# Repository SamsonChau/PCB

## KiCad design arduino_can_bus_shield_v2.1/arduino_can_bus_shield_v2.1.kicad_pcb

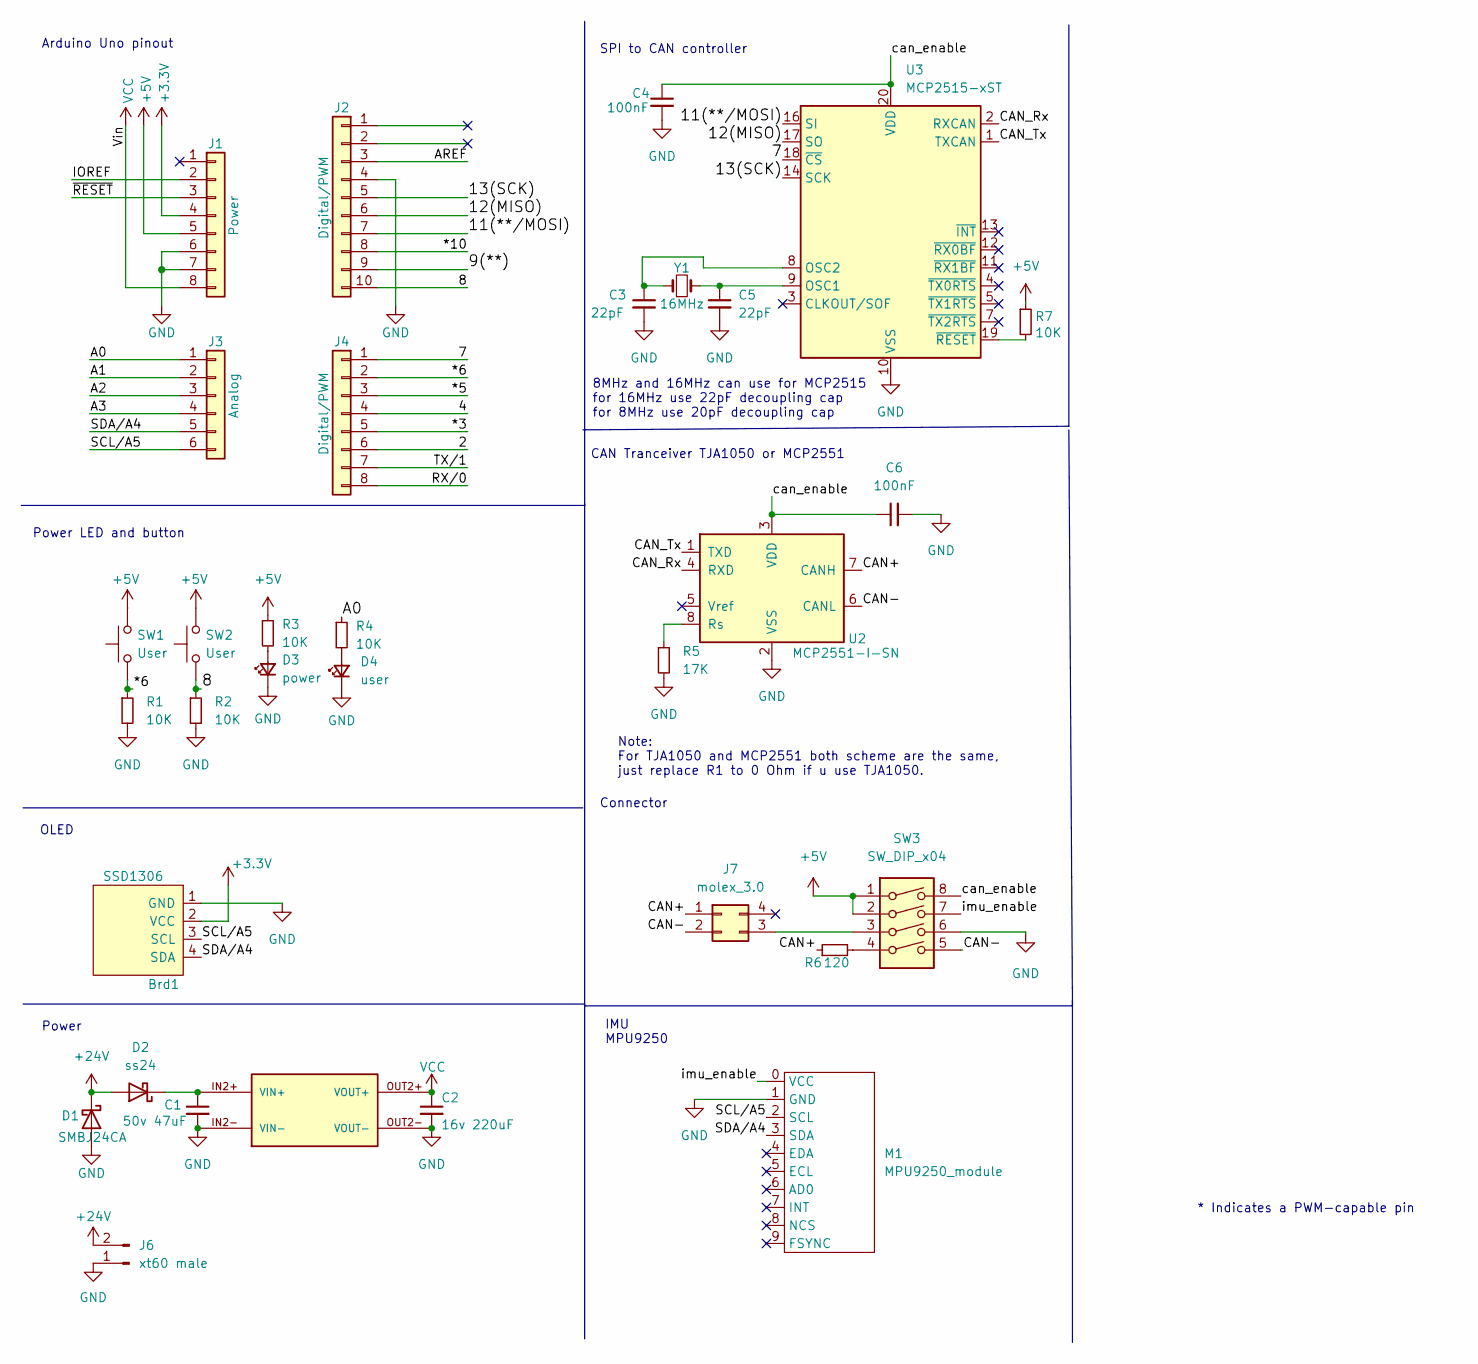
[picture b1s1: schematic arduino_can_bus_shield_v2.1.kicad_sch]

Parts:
Brd1: SSD1306; 128x64OLED
C1: 50v 47uF; C_Elec_6.3x7.7
C2: 16v 220uF; C_Elec_6.3x7.7
C3, C5: 22pF; C_0805_2012Metric_Pad1.18x1.45mm_HandSolder
C4, C6: 100nF; C_0805_2012Metric_Pad1.18x1.45mm_HandSolder
D1: SMBJ24CA; D_SMB_Handsoldering
D2: ss24; D_SMB_Handsoldering
D3: power; LED_0805_2012Metric_Pad1.15x1.40mm_HandSolder
D4: user; LED_0805_2012Metric_Pad1.15x1.40mm_HandSolder
J1: Power; PinSocket_1x08_P2.54mm_Vertical
J2: Digital/PWM; PinSocket_1x10_P2.54mm_Vertical
J3: Analog; PinSocket_1x06_P2.54mm_Vertical
J4: Digital/PWM; PinSocket_1x08_P2.54mm_Vertical
J6: xt60 male; XT60PW-M20
J7: molex_3.0; Molex_Micro-Fit_3.0_43045-0400_2x02_P3.00mm_Horizontal
M1: MPU9250_module
R1, R2, R3, R4, R7: 10K; R_0805_2012Metric_Pad1.20x1.40mm_HandSolder
R5: 17K; R_0805_2012Metric_Pad1.20x1.40mm_HandSolder
R6: 120; R_0805_2012Metric_Pad1.20x1.40mm_HandSolder
SW1: User; SW_SPST_TL3305A
SW2: User; SW_SPST_TL3305C
SW3: SW_DIP_x04; SW_DIP_SPSTx04_Slide_9.78x12.34mm_W7.62mm_P2.54mm
U1: MP1584; DC-DC-mp1584_module
U2: MCP2551-I-SN; SOIC-8_3.9x4.9mm_P1.27mm
U3: MCP2515-xST; TSSOP-20_4.4x6.5mm_P0.65mm
Y1: 16MHz; Crystal_SMD_HC49-SD

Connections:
+3V3: Brd1.2 (VCC), J1.4
+5V: J1.5, R3.1, R7.1, SW1.2, SW2.2, SW3.1, SW3.2
+24V: D1.1 (K), D2.2 (A), J6.2
/2: J4.6
/4: J4.4
/7: J4.1, U3.18 (~CS)
/8: J2.10, R2.1, SW2.1
/9(**): J2.9
/11(**/MOSI): J2.7, U3.16 (SI)
/12(MISO): J2.6, U3.17 (SO)
/13(SCK): J2.5, U3.14 (SCK)
/*3: J4.5
/*5: J4.3
/*6: J4.2, R1.1, SW1.1
/*10: J2.8
/A0: J3.1, R4.1
/A1: J3.2
/A2: J3.3
/A3: J3.4
/AREF: J2.3
/CAN+: J7.1, R6.1, U2.7 (CANH)
/CAN-: J7.2, SW3.5, U2.6 (CANL)
/CAN_Rx: U2.4 (RXD), U3.2 (RXCAN)
/CAN_Tx: U2.1 (TXD), U3.1 (TXCAN)
/IOREF: J1.2
/RX/0: J4.8
/SCL/A5: Brd1.3 (SCL), J3.6, M1.2 (SCL)
/SDA/A4: Brd1.4 (SDA), J3.5, M1.3 (SDA)
/TX/1: J4.7
/can_enable: C4.1, C6.1, SW3.8, U2.3 (VDD), U3.20 (VDD)
/imu_enable: M1.0 (VCC), SW3.7
/~RESET: J1.3
GND: Brd1.1 (GND), C1.2, C2.2, C3.2, C4.2, C5.2, C6.2, D1.2 (A), D3.1 (K), D4.1 (K), J1.6, J1.7, J2.4, J6.1, M1.1 (GND), R1.2, R2.2, R5.2, SW3.6, U1.IN2- (VIN-), U1.OUT2- (VOUT-), U2.2 (VSS), U3.10 (VSS)
unnamed: C1.1, D2.1 (K), U1.IN2+ (VIN+)
unnamed: C3.1, U3.8 (OSC2), Y1.1
unnamed: C5.1, U3.9 (OSC1), Y1.2
unnamed: D3.2 (A), R3.2
unnamed: D4.2 (A), R4.2
unnamed: J7.3, SW3.3
unnamed: R5.1, U2.8 (Rs)
unnamed: R6.2, SW3.4
unnamed: R7.2, U3.19 (~RESET)
VCC: C2.1, J1.8, U1.OUT2+ (VOUT+)

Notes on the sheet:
IMU MPU9250
Note: For TJA1050 and MCP2551 both scheme are the same, just replace R1 to 0 Ohm if u use TJA1050.
SPI to CAN controller
Arduino Uno pinout
8MHz and 16MHz can use for MCP2515 for 16MHz use 22pF decoupling cap for 8MHz use 20pF decoupling cap
OLED
Power LED and button
* Indicates a PWM-capable pin
Power
Connector
CAN Tranceiver TJA1050 or MCP2551

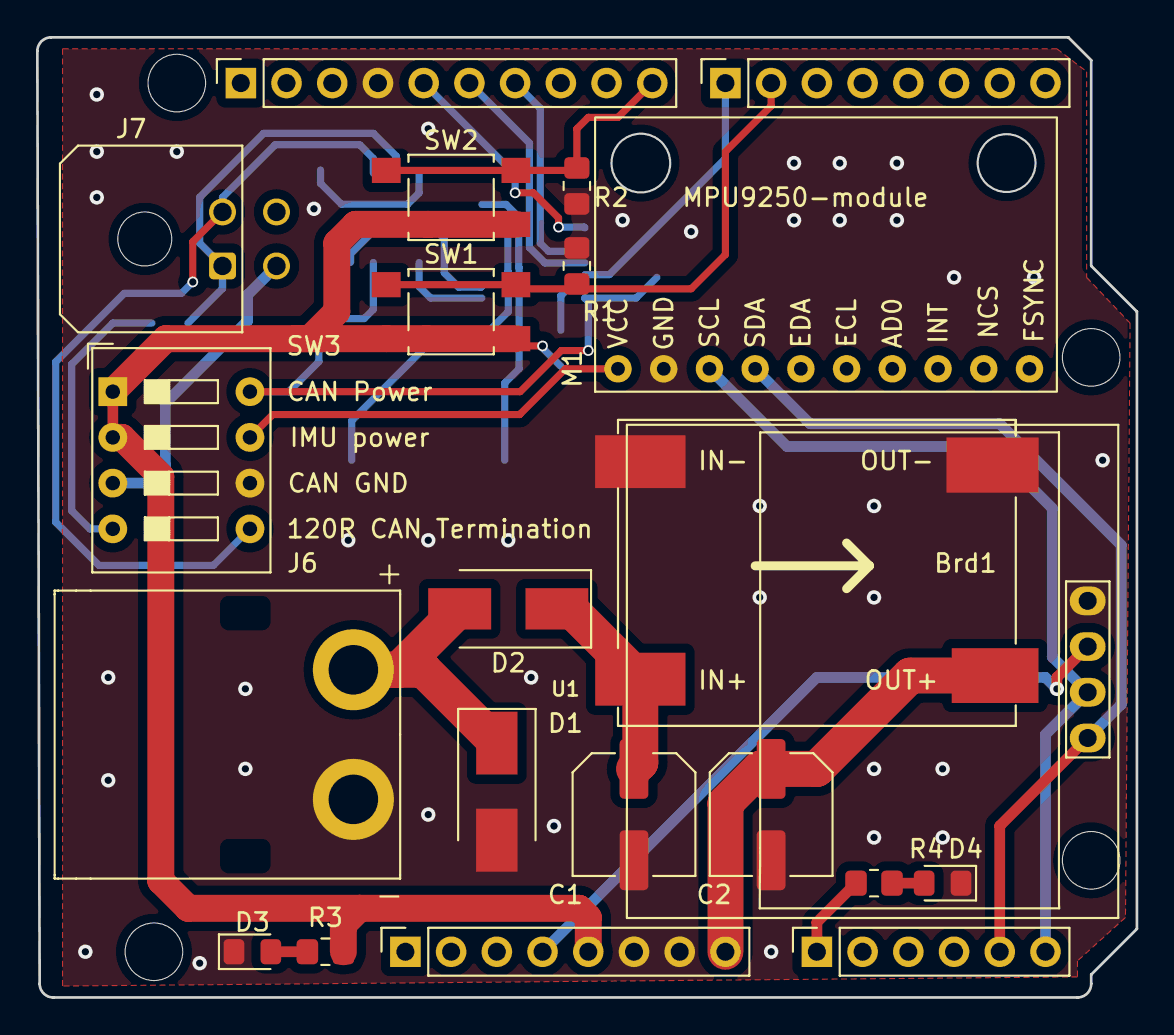
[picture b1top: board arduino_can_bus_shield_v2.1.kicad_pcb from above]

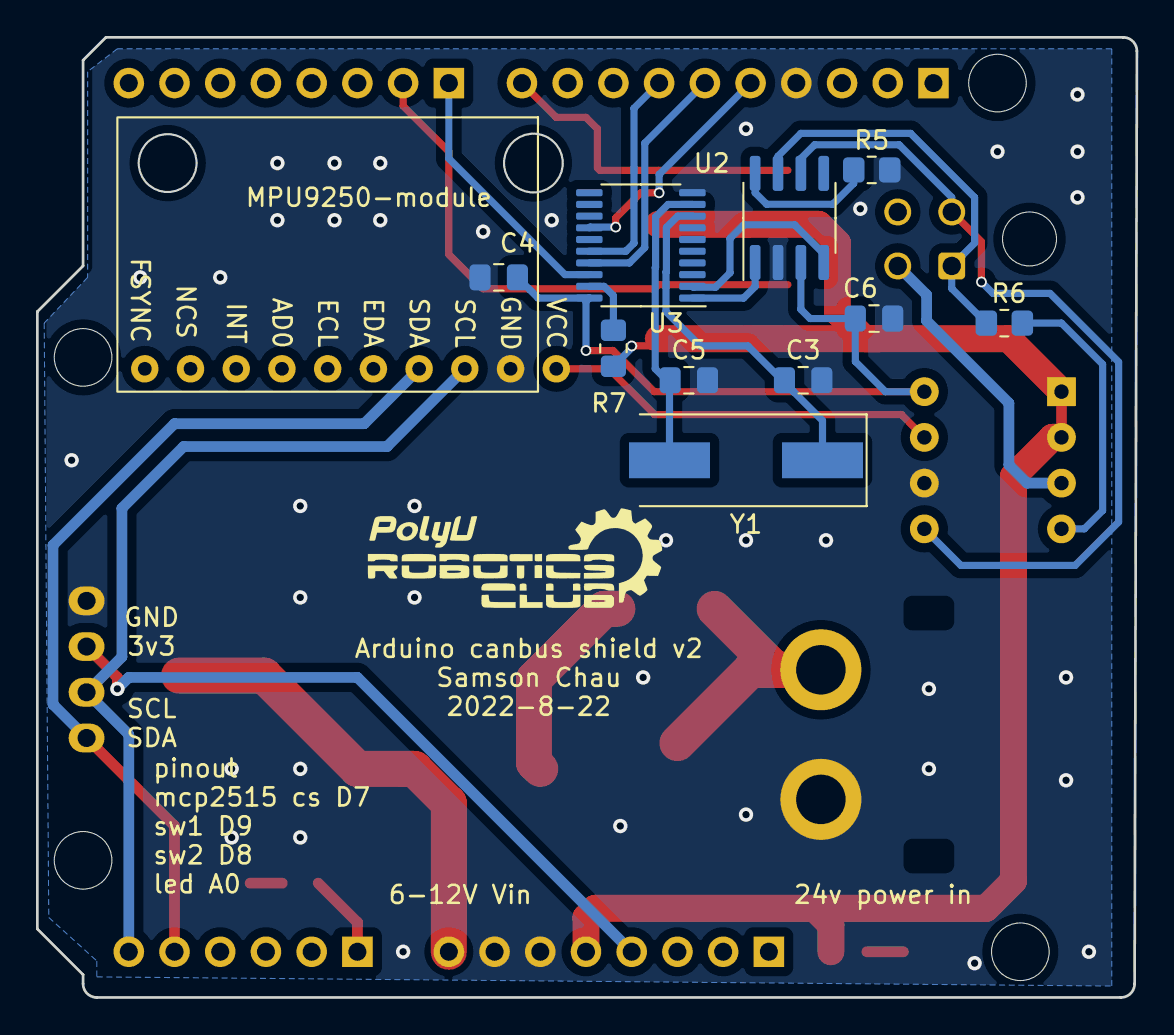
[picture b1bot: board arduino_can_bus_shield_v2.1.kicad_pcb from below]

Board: 2 copper layers, 61.1 x 53.3 mm, 36 parts (10 on the bottom side), 29 nets.

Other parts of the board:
MH1, MH2, MH3, MH4: MountingHole_3.2mm

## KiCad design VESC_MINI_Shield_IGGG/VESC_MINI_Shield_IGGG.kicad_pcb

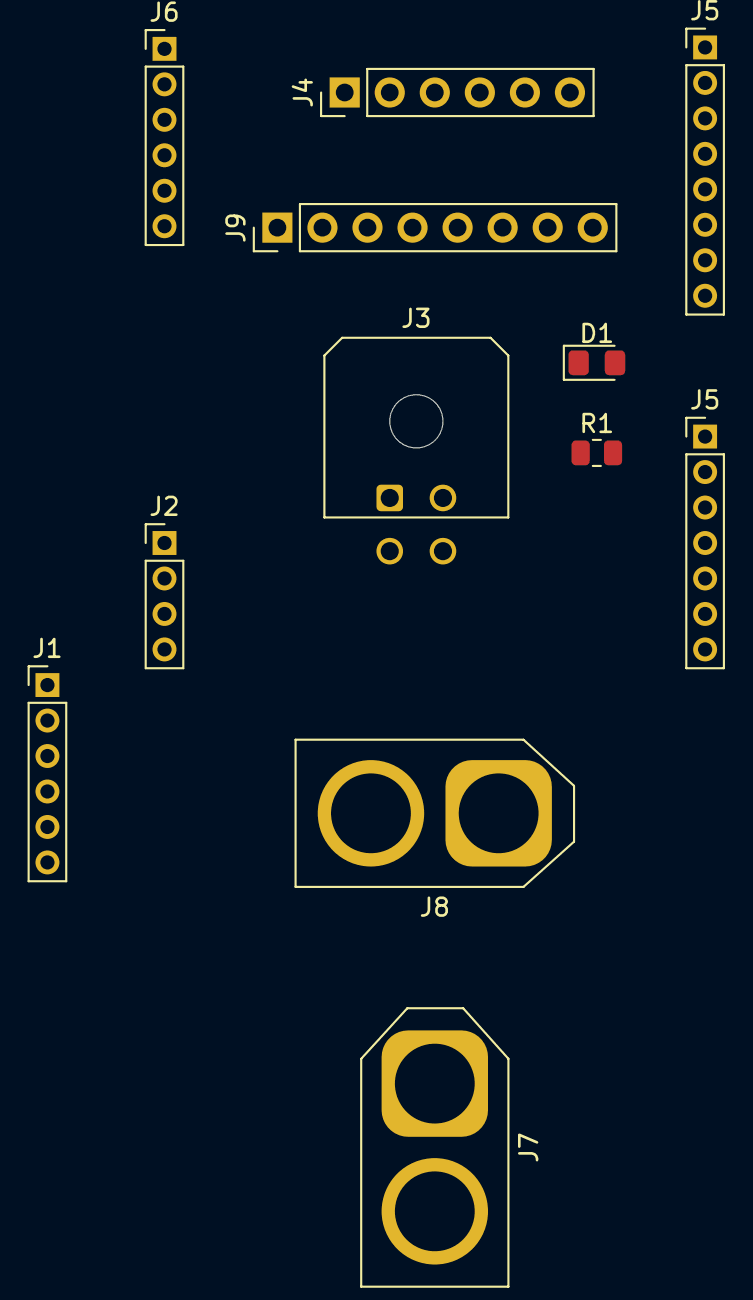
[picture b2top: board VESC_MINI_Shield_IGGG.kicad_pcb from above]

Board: 2 copper layers, 12 parts (0 on the bottom side), 17 nets, no tracks yet.

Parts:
D1: PWR; LED_0805_2012Metric_Pad1.15x1.40mm_HandSolder
J1: Sensor; PinHeader_1x06_P2.00mm_Vertical
J2: CAN; PinHeader_1x04_P2.00mm_Vertical
J3: CAN_MOLEX; Molex_Micro-Fit_3.0_43045-0400_2x02_P3.00mm_Horizontal
J4: Encoder 1; PinHeader_1x06_P2.54mm_Vertical
J5: Comm; PinHeader_1x08_P2.00mm_Vertical
J5#2: General; PinHeader_1x07_P2.00mm_Vertical
J6: NC; PinHeader_1x06_P2.00mm_Vertical
J7: XT60 IN; AMASS_XT60-M_1x02_P7.20mm_Vertical
J8: XT60 OUT; AMASS_XT60-F_1x02_P7.20mm_Vertical
J9: Encoder_out_port_8pin; PinHeader_1x08_P2.54mm_Vertical
R1: 3.3K; R_0805_2012Metric

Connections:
+3.3V: D1.2 (A), J5.2, J5#2.2, J9.2
+5V: J1.6, J2.4
+24V: J7.1, J8.1
/5V: J4.6, J5.1, J9.1
/ADC1: J5.8, J9.8
/CANH: J2.3, J3.1
/CANL: J2.2, J3.2
/H1: J1.4, J4.4
/H2: J1.3, J4.3
/H3: J1.2, J4.2
/MOSI/ADC2: J5.7, J9.7
/RX/SDA/NSS: J5.5, J9.5
/SCK/ADC: J5.4, J9.4
/TMP: J1.5, J4.5
/TX/SCL/MOSI: J5.6, J9.6
GND: J1.1, J2.1, J5.3, J5#2.3, J7.2, J8.2, J9.3, R1.2
unnamed: D1.1 (K), R1.1

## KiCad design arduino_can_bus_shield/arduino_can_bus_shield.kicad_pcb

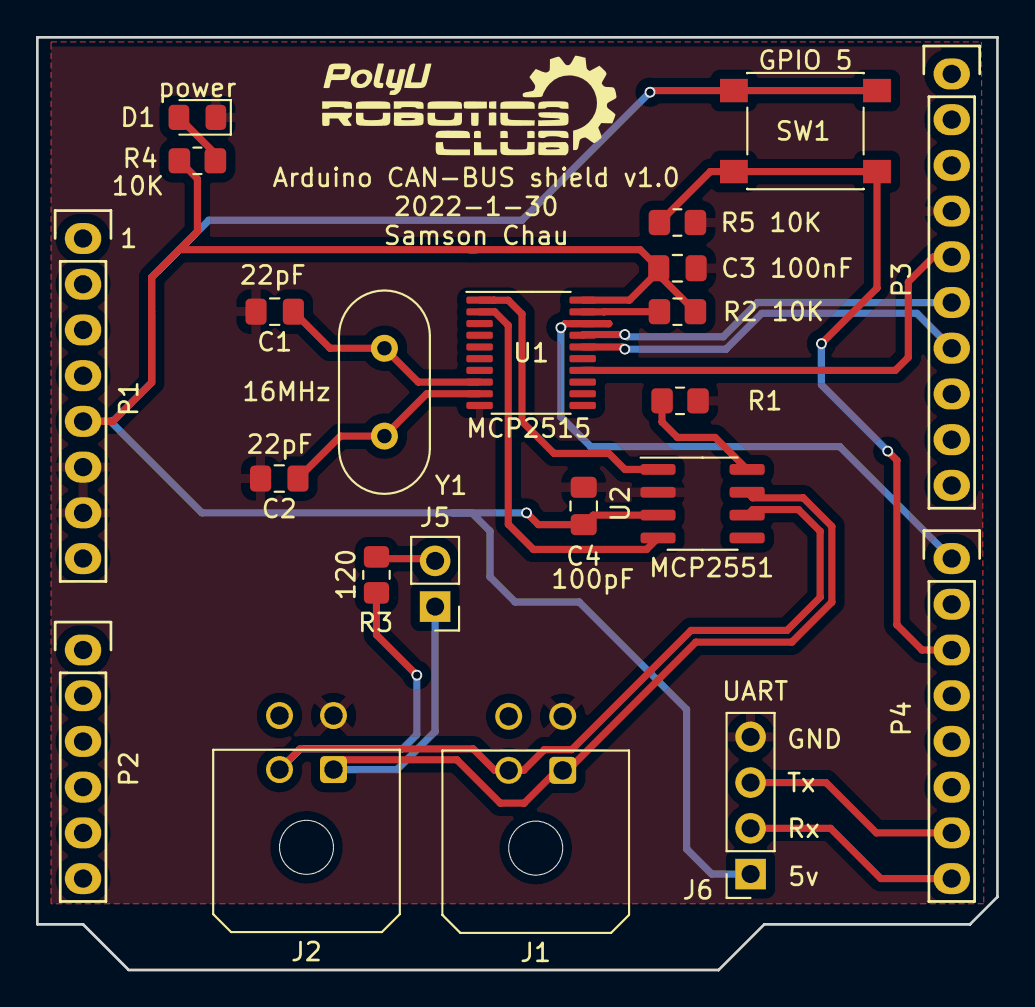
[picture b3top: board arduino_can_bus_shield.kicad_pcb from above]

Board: 2 copper layers, 53.3 x 51.8 mm, 22 parts (0 on the bottom side), 19 nets.

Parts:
C1, C2: 22pF; C_0805_2012Metric_Pad1.18x1.45mm_HandSolder
C3 100nF, C4: 100nF; C_0805_2012Metric_Pad1.18x1.45mm_HandSolder
D1: power; LED_0805_2012Metric_Pad1.15x1.40mm_HandSolder
J1, J2: molex_3.0; Molex_Micro-Fit_3.0_43045-0400_2x02_P3.00mm_Horizontal
J5: jumper; PinHeader_1x02_P2.54mm_Vertical
J6: UART2; PinSocket_1x04_P2.54mm_Vertical
P1: Power; Socket_Strip_Arduino_1x08
P2: Analog; Socket_Strip_Arduino_1x06
P3: Digital; Socket_Strip_Arduino_1x10
P4: Digital; Socket_Strip_Arduino_1x08
R1: 17K; R_0805_2012Metric_Pad1.20x1.40mm_HandSolder
R2 10K, R4, R5 10K: 10K; R_0805_2012Metric_Pad1.20x1.40mm_HandSolder
R3: 120; R_0805_2012Metric_Pad1.20x1.40mm_HandSolder
SW1: User; SW_Push_1P1T_NO_6x6mm_H9.5mm
U1: MCP2515-xST; TSSOP-20_4.4x6.5mm_P0.65mm
U2: MCP2551-I-SN; SOIC-8_3.9x4.9mm_P1.27mm
Y1: 16MHz; Crystal_HC49-U_Vertical

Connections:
+5V: C3 100nF.1, C4.1, J6.1, P1.5, R2 10K.1, R4.1, SW1.2, U1.20 (VDD), U2.3 (VDD)
/0(Rx): J6.2, P4.8
/1(Tx): J6.3, P4.7
/5(**): P4.3, R5 10K.1, SW1.1
/7: P4.1, U1.18 (~CS)
/11(**/MOSI): P3.7, U1.16 (SI)
/12(MISO): P3.6, U1.17 (SO)
/13(SCK): P3.5, U1.14 (SCK)
/CAN+: J1.1, J2.1, J5.1, U2.7 (CANH)
/CAN-: J1.2, J2.2, R3.2, U2.6 (CANL)
/CAN_Rx: U1.2 (RXCAN), U2.4 (RXD)
/CAN_Tx: U1.1 (TXCAN), U2.1 (TXD)
GND: C1.2, C2.2, C3 100nF.2, C4.2, D1.1 (K), J1.3, J2.3, J6.4, P1.6, P1.7, P3.4, R1.2, R5 10K.2, U1.10 (VSS), U2.2 (VSS)
unnamed: C1.1, U1.8 (OSC2), Y1.1
unnamed: C2.1, U1.9 (OSC1), Y1.2
unnamed: D1.2 (A), R4.2
unnamed: J5.2, R3.1
unnamed: R1.1, U2.8 (Rs)
unnamed: R2 10K.2, U1.19 (~RESET)

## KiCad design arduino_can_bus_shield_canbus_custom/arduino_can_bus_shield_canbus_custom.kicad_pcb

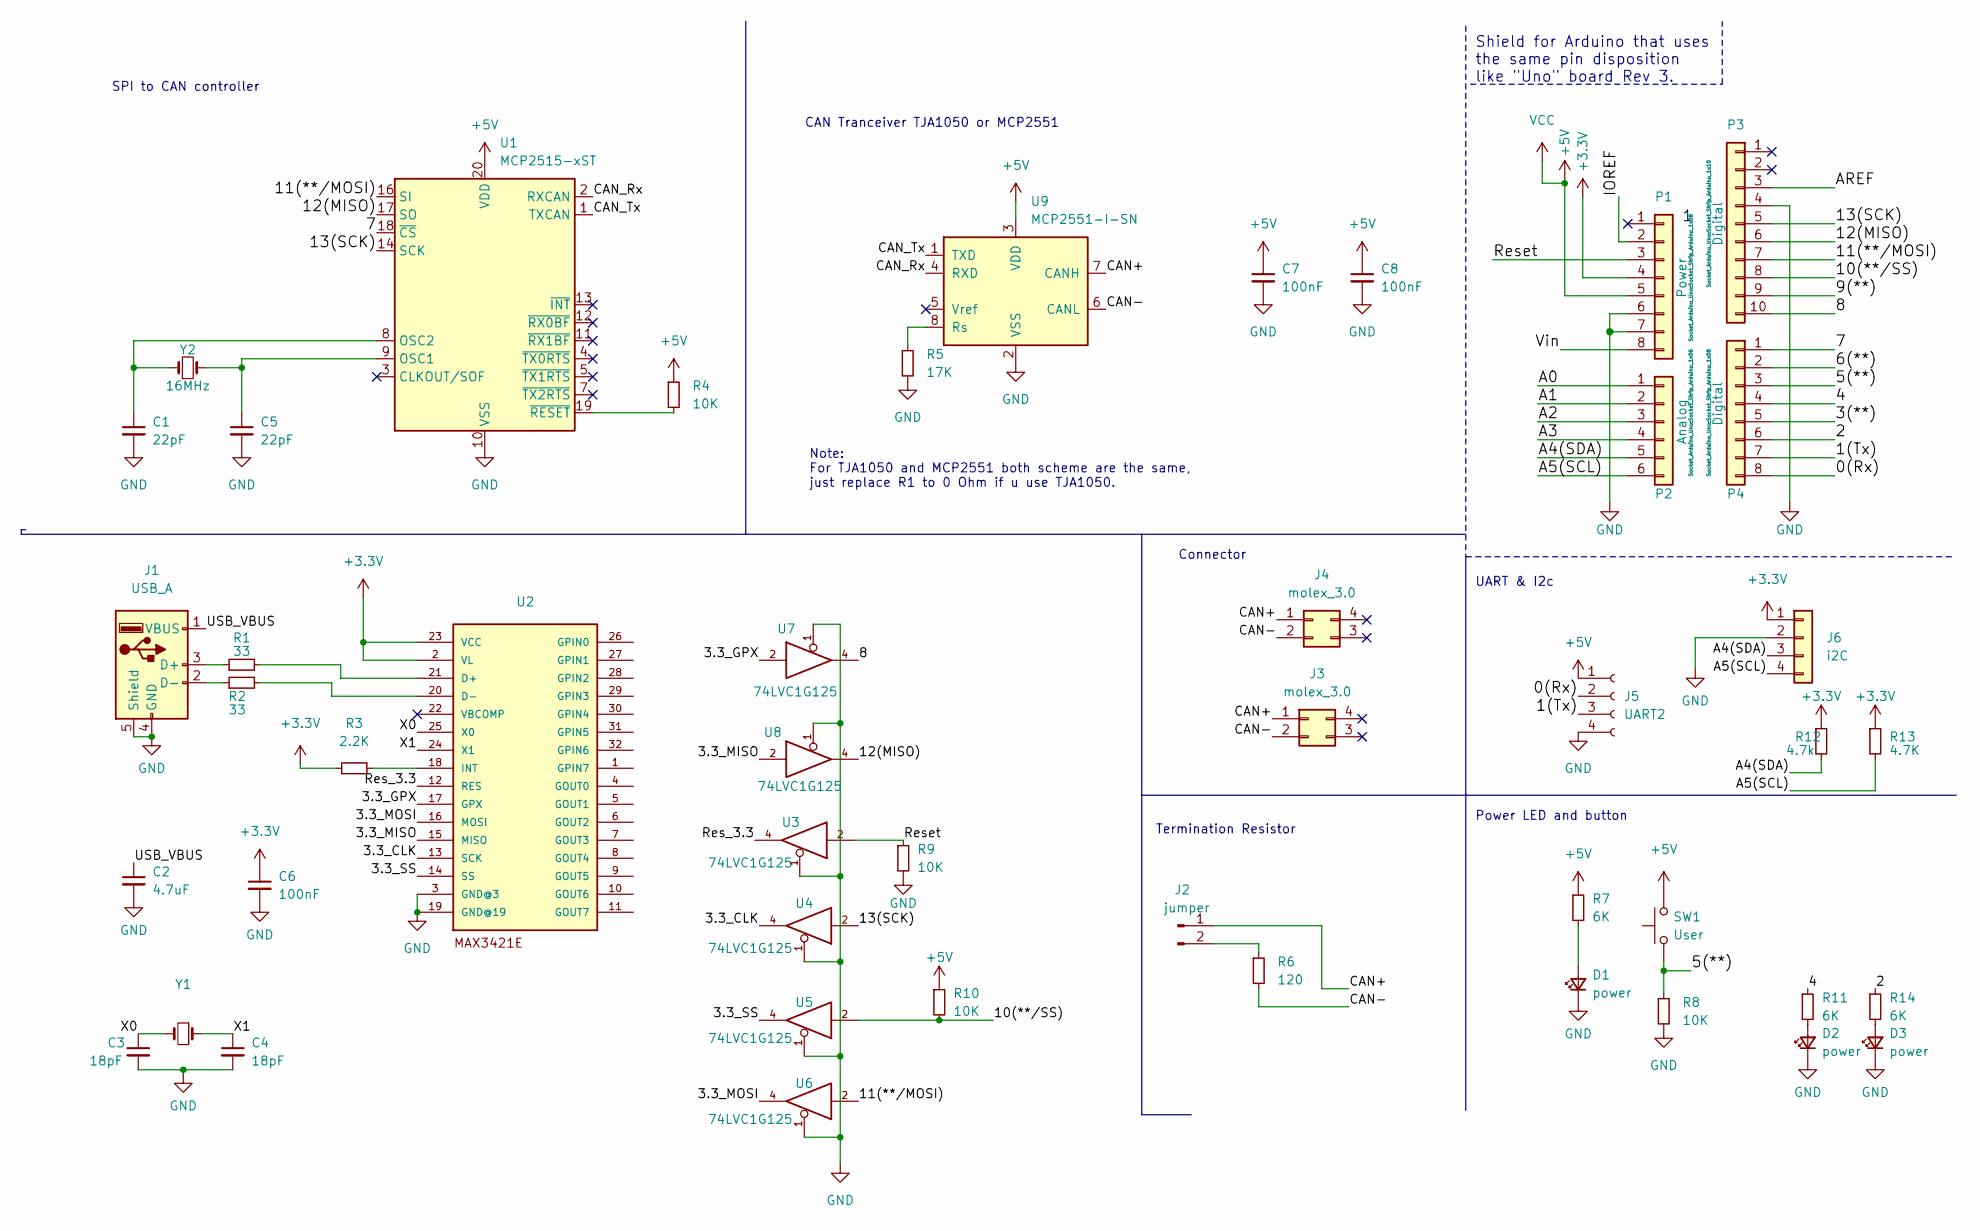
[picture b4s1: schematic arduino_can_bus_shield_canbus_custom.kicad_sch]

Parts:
C1, C5: 22pF; C_0805_2012Metric_Pad1.18x1.45mm_HandSolder
C2: 4.7uF; C_0805_2012Metric
C3, C4: 18pF; C_0805_2012Metric
C6: 100nF; C_0805_2012Metric
C7, C8: 100nF; C_0805_2012Metric_Pad1.18x1.45mm_HandSolder
D1, D2, D3: power; LED_0805_2012Metric_Pad1.15x1.40mm_HandSolder
J1: USB_A; USB_A_Molex_67643_Horizontal
J2: jumper; PinHeader_1x02_P2.54mm_Vertical
J3, J4: molex_3.0; Molex_Micro-Fit_3.0_43045-0400_2x02_P3.00mm_Horizontal
J5: UART2; PinSocket_1x04_P2.54mm_Vertical
J6: i2C; PinHeader_1x04_P2.54mm_Vertical
P1: Power; Socket_Strip_Arduino_1x08
P2: Analog; Socket_Strip_Arduino_1x06
P3: Digital; Socket_Strip_Arduino_1x10
P4: Digital; Socket_Strip_Arduino_1x08
R1, R2: 33; R_0805_2012Metric
R3: 2.2K; R_0805_2012Metric
R4, R8: 10K; R_0805_2012Metric_Pad1.20x1.40mm_HandSolder
R5: 17K; R_0805_2012Metric_Pad1.20x1.40mm_HandSolder
R6: 120; R_0805_2012Metric_Pad1.20x1.40mm_HandSolder
R7, R11, R14: 6K; R_0805_2012Metric_Pad1.20x1.40mm_HandSolder
R9, R10: 10K; R_0805_2012Metric
R12: 4.7k; R_0805_2012Metric
R13: 4.7K; R_0805_2012Metric
SW1: User; SW_Push_1P1T_NO_6x6mm_H9.5mm
U1: MCP2515-xST; TSSOP-20_4.4x6.5mm_P0.65mm
U2: MAX3421E; TQFP32-5MM
U3, U4, U5, U6, U7, U8: 74LVC1G125; SOT-353_SC-70-5_Handsoldering
U9: MCP2551-I-SN; SOIC-8_3.9x4.9mm_P1.27mm
Y1: Crystal_SMD_HC49-SD
Y2: 16MHz; Crystal_HC49-U_Vertical

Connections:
+3V3: C6.1, J6.1, P1.4, R3.1, R12.1, R13.1, U2.2 (VL), U2.23 (VCC)
+5V: C7.1, C8.1, J5.1, P1.5, R4.1, R7.1, R10.1, SW1.2, U1.20 (VDD), U3.5 (VCC), U4.5 (VCC), U5.5 (VCC), U6.5 (VCC), U7.5 (VCC), U8.5 (VCC), U9.3 (VDD)
/0(Rx): J5.2, P4.8
/1(Tx): J5.3, P4.7
/2: P4.6, R14.1
/3(**): P4.5
/3.3_CLK: U2.13 (SCK), U4.4
/3.3_GPX: U2.17 (GPX), U7.2
/3.3_MISO: U2.15 (MISO), U8.2
/3.3_MOSI: U2.16 (MOSI), U6.4
/3.3_SS: U2.14 (SS), U5.4
/4: P4.4, R11.1
/5(**): P4.3, R8.1, SW1.1
/6(**): P4.2
/7: P4.1, U1.18 (~CS)
/8: P3.10, U7.4
/9(**): P3.9
/12(MISO): P3.6, U1.17 (SO), U8.4
/13(SCK): P3.5, U1.14 (SCK), U4.2
/A0: P2.1
/A1: P2.2
/A2: P2.3
/A3: P2.4
/A4(SDA): J6.3, P2.5, R12.2
/A5(SCL): J6.4, P2.6, R13.2
/AREF: P3.3
/CAN+: J2.1, J3.1, J4.1, U9.7 (CANH)
/CAN-: J3.2, J4.2, R6.2, U9.6 (CANL)
/CAN_Rx: U1.2 (RXCAN), U9.4 (RXD)
/CAN_Tx: U1.1 (TXCAN), U9.1 (TXD)
/IOREF: P1.2
/Res_3.3: U2.12 (RES), U3.4
/Reset: P1.3, R9.1, U3.2
/USB_VBUS: C2.1, J1.1 (VBUS)
/Vin: P1.8
/X0: C3.1, U2.25 (X0), Y1.2
/X1: C4.1, U2.24 (X1), Y1.1
GND: C1.2, C2.2, C3.2, C4.2, C5.2, C6.2, C7.2, C8.2, D1.1 (K), D2.1 (K), D3.1 (K), J1.4 (GND), J1.5 (Shield), J5.4, J6.2, P1.6, P1.7, P3.4, R5.2, R8.2, R9.2, U1.10 (VSS), U2.3 (GND@3), U2.19 (GND@19), U3.1, U3.3 (GND), U4.1, U4.3 (GND), U5.1, U5.3 (GND), U6.1, U6.3 (GND), U7.1, U7.3 (GND), U8.1, U8.3 (GND), U9.2 (VSS)
unnamed: C1.1, U1.8 (OSC2), Y2.1
unnamed: C5.1, U1.9 (OSC1), Y2.2
unnamed: D1.2 (A), R7.2
unnamed: D2.2 (A), R11.2
unnamed: D3.2 (A), R14.2
unnamed: J1.2 (D-), R2.1
unnamed: J1.3 (D+), R1.1
unnamed: J2.2, R6.1
unnamed: R1.2, U2.21 (D+)
unnamed: R2.2, U2.20 (D-)
unnamed: R3.2, U2.18 (INT)
unnamed: R4.2, U1.19 (~RESET)
unnamed: R5.1, U9.8 (Rs)

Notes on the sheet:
Termination Resistor
CAN Tranceiver TJA1050 or MCP2551
Shield for Arduino that uses the same pin disposition like "Uno" board Rev 3.
Note: For TJA1050 and MCP2551 both scheme are the same, just replace R1 to 0 Ohm if u use TJA1050.
Connector
UART & I2c
SPI to CAN controller
Power LED and button

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
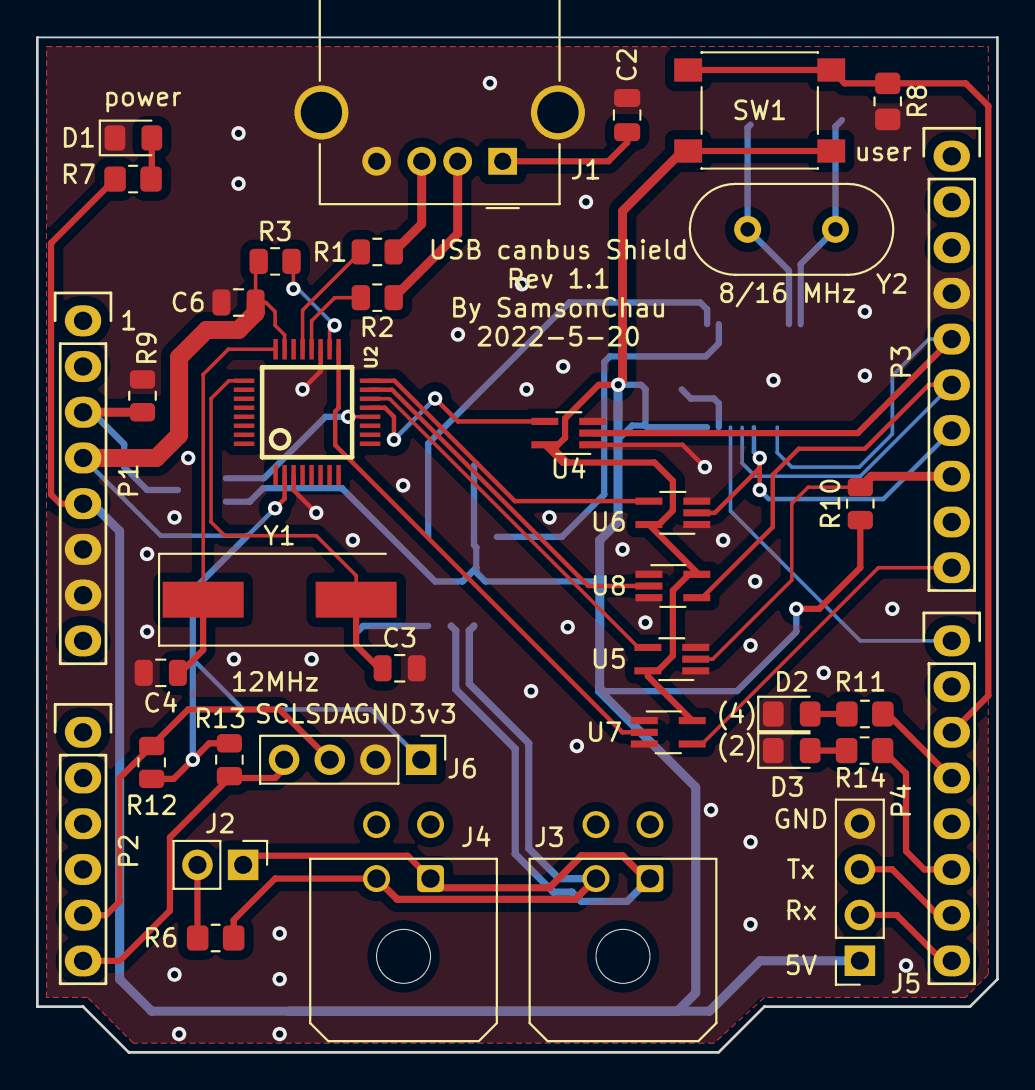
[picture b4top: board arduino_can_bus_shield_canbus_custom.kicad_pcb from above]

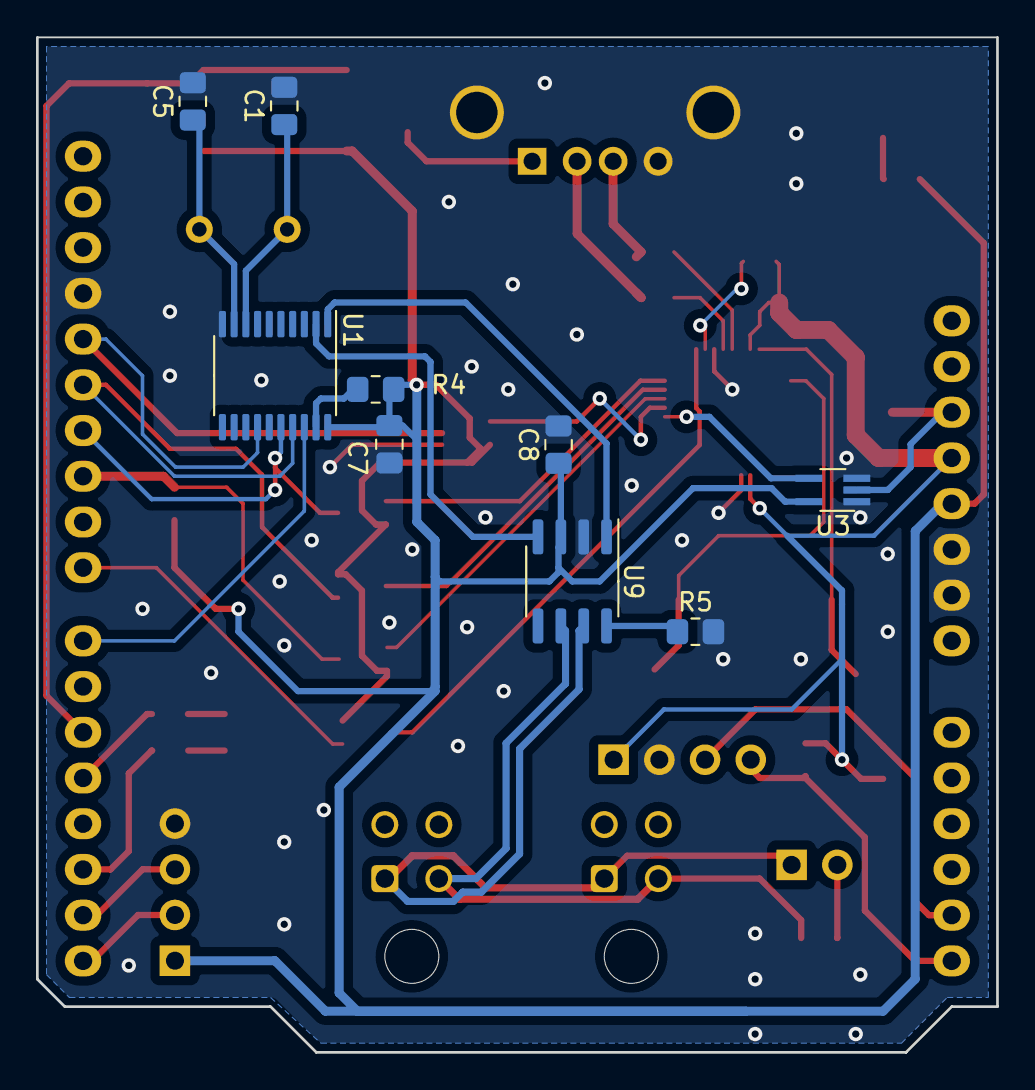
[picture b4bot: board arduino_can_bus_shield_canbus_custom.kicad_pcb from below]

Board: 2 copper layers, 53.3 x 56.4 mm, 47 parts (9 on the bottom side), 43 nets.

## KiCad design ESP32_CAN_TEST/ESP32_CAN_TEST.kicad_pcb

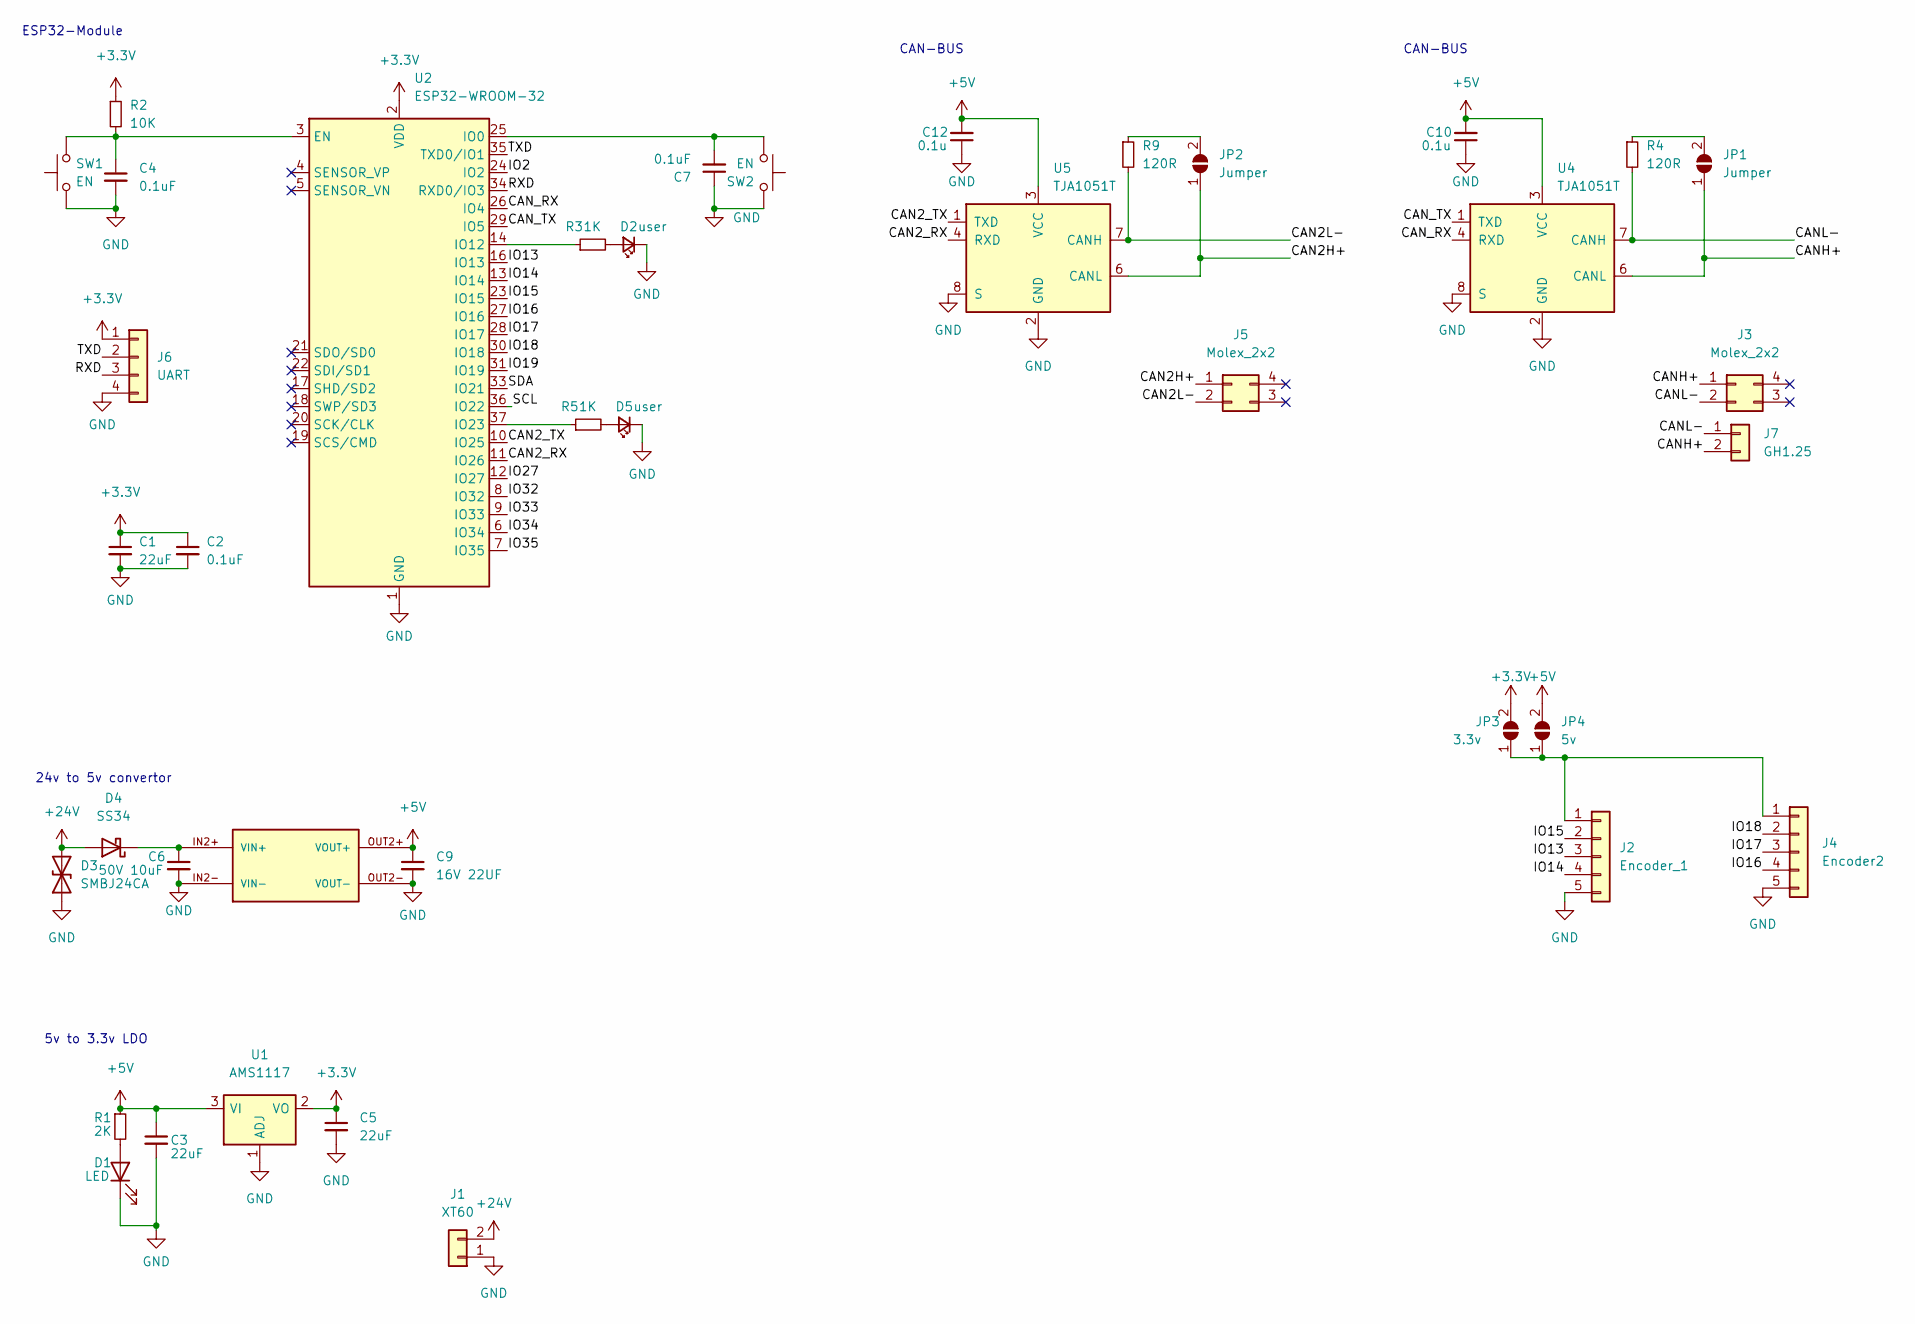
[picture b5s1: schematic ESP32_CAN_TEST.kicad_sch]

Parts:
C1, C3, C5: 22uF; C_0805_2012Metric
C2, C4, C7: 0.1uF; C_0805_2012Metric
C6: 50V 10uF; CP_Elec_6.3x7.7
C9: 16V 22UF; CP_Elec_6.3x7.7
C10, C12: 0.1u; C_0805_2012Metric
D1: LED; LED_0805_2012Metric_Pad1.15x1.40mm_HandSolder
D2, D5: user; LED_0805_2012Metric
D3: SMBJ24CA; D_SMB
D4: SS34; D_SMB
J1: XT60; AMASS_XT30U-M_1x02_P5.0mm_Vertical
J2: Encoder_1; PinHeader_1x05_P2.54mm_Vertical
J3, J5: Molex_2x2; Molex_Micro-Fit_3.0_43045-0412_2x02_P3.00mm_Vertical
J4: Encoder2; PinHeader_1x05_P2.54mm_Vertical
J6: UART; PinSocket_1x04_P2.54mm_Vertical
J7: GH1.25; JST_GH_BM02B-GHS-TBT_1x02-1MP_P1.25mm_Vertical
JP1, JP2: Jumper; SolderJumper-2_P1.3mm_Open_Pad1.0x1.5mm
JP3: 3.3v; SolderJumper-2_P1.3mm_Open_Pad1.0x1.5mm
JP4: 5v; SolderJumper-2_P1.3mm_Open_Pad1.0x1.5mm
R1: 2K; R_0805_2012Metric_Pad1.20x1.40mm_HandSolder
R2: 10K; R_0805_2012Metric_Pad1.20x1.40mm_HandSolder
R3, R5: 1K; R_0805_2012Metric_Pad1.20x1.40mm_HandSolder
R4, R9: 120R; R_0805_2012Metric_Pad1.20x1.40mm_HandSolder
SW1, SW2: EN; SW_SPST_TL3342
U1: AMS1117; SOT-223-3_TabPin2
U2: ESP32-WROOM-32
U3: MP1584; DC-DC-mp1584_module
U4, U5: TJA1051T; SOIC-8_3.9x4.9mm_P1.27mm

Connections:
+5V: C3.1, C9.1, C10.2, C12.2, JP4.2 (B), R1.1, U1.3 (VI), U3.OUT2+ (VOUT+), U4.3 (VCC), U5.3 (VCC)
+24V: D3.2 (A2), D4.2 (A), J1.2
/CAN2H+: J5.1, JP2.1 (A), U5.6 (CANL)
/CAN2L-: J5.2, R9.2, U5.7 (CANH)
/CAN2_RX: U2.11 (IO26), U5.4 (RXD)
/CAN2_TX: U2.10 (IO25), U5.1 (TXD)
/CANH+: J3.1, J7.2, JP1.1 (A), U4.6 (CANL)
/CANL-: J3.2, J7.1, R4.2, U4.7 (CANH)
/CAN_RX: U2.26 (IO4), U4.4 (RXD)
/CAN_TX: U2.29 (IO5), U4.1 (TXD)
/IO2: U2.24 (IO2)
/IO13: J2.3, U2.16 (IO13)
/IO14: J2.4, U2.13 (IO14)
/IO15: J2.2, U2.23 (IO15)
/IO16: J4.4, U2.27 (IO16)
/IO17: J4.3, U2.28 (IO17)
/IO18: J4.2, U2.30 (IO18)
/IO19: U2.31 (IO19)
/IO27: U2.12 (IO27)
/IO32: U2.8 (IO32)
/IO33: U2.9 (IO33)
/IO34: U2.6 (IO34)
/IO35: U2.7 (IO35)
/RXD: J6.3, U2.34 (RXD0/IO3)
/SCL: U2.36 (IO22)
/SDA: U2.33 (IO21)
/TXD: J6.2, U2.35 (TXD0/IO1)
GND: C1.2, C2.2, C3.2, C4.2, C5.2, C6.2, C7.1, C9.2, C10.1, C12.1, D1.1 (K), D2.1 (K), D3.1 (A1), D5.1 (K), J1.1, J2.5, J4.5, J6.4, SW1.1, SW2.2, U1.1 (ADJ), U2.1 (GND), U2.15 (GND), U2.38 (GND), U2.39 (GND), U3.IN2- (VIN-), U3.OUT2- (VOUT-), U4.2 (GND), U4.8 (S), U5.2 (GND), U5.8 (S)
unnamed: C4.1, R2.2, SW1.2, U2.3 (EN)
unnamed: C6.1, D4.1 (K), U3.IN2+ (VIN+)
unnamed: C7.2, SW2.1, U2.25 (IO0)
unnamed: D1.2 (A), R1.2
unnamed: D2.2 (A), R3.2
unnamed: D5.2 (A), R5.2
unnamed: J2.1, J4.1, JP3.1 (A), JP4.1 (A)
unnamed: JP1.2 (B), R4.1
unnamed: JP2.2 (B), R9.1
unnamed: R3.1, U2.14 (IO12)
unnamed: R5.1, U2.37 (IO23)

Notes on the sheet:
5v to 3.3v LDO
ESP32-Module
CAN-BUS
24v to 5v convertor

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
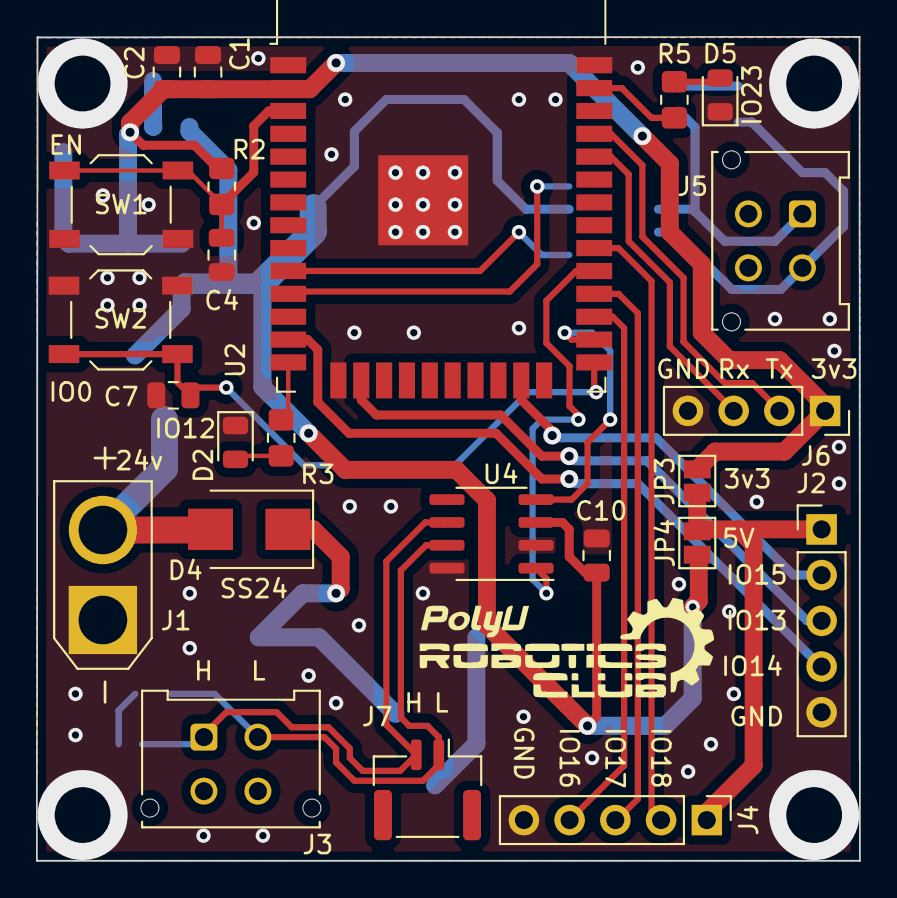
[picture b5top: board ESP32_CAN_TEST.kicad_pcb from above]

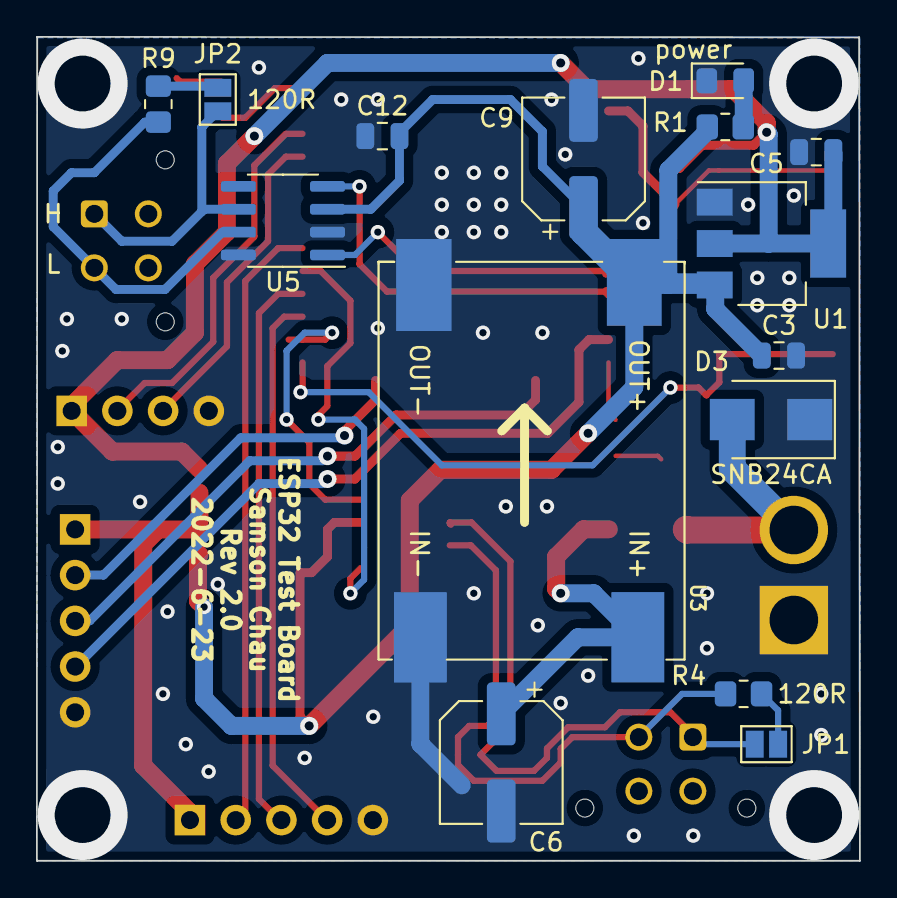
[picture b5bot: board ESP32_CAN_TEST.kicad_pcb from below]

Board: 2 copper layers, 45.7 x 45.8 mm, 39 parts (15 on the bottom side), 31 nets.
